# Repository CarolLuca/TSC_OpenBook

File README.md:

# OpenBook

## Introduction

OpenBook is an energy-efficient e-book reader designed with open-source principles, featuring Wi-Fi connectivity and environmental sensing capabilities. The device emphasizes a minimalist design, providing a distraction-free reading experience through a high-contrast e-paper display that mimics real paper, reducing eye strain during extended reading sessions.

## Block Diagram

## Hardware Description

### Microcontroller

The OpenBook is built around the **ESP32-C6-WROOM-1-N8** microcontroller:
- 32-bit RISC-V single-core processor running at up to 160MHz
- 320KB ROM, 512KB HP SRAM, 16KB LP SRAM
- Built-in Wi-Fi 6 and Bluetooth LE 5.0 connectivity
- Support for various interfaces: GPIO, SPI, UART, I2C, PWM
- Operating voltage: 3.3V

The ESP32-C6 offers excellent power efficiency with multiple power modes:
- Active mode: 160-260mA (when running at full capacity)
- Modem sleep: 3-20mA (Wi-Fi radio disabled)
- Light sleep: 0.8mA
- Deep sleep: 10μA (core powered down, wake sources active)
- Hibernation: 2.5μA (minimal functions active)

### Display Interface

The OpenBook connects to a 7.5" E-Paper Display through an FPC connector. The display communicates via SPI:
- EPD_CS connected to ESP32-C6 GPIO10
- EPD_DC connected to ESP32-C6 GPIO5
- EPD_RST connected to ESP32-C6 GPIO23
- EPD_BUSY connected to ESP32-C6 GPIO3
- MOSI, SCK shared with SD card interface

The e-paper display was chosen for its paper-like appearance, ultra-low power consumption (only requires power during page refreshes), and excellent readability in direct sunlight.

### Storage Solutions

The OpenBook features dual storage solutions:

1. **MicroSD Card Interface** (primary storage for e-books):
   - Connected via SPI protocol
   - Card Detect/DAT3 connected to ESP32-C6 GPIO4
   - CMD connected to ESP32-C6 GPIO7 (MOSI for SPI)
   - DAT0 connected to ESP32-C6 GPIO2 (MISO for SPI)
   - CLK connected to ESP32-C6 GPIO6 (SCK for SPI)
   
2. **64MB NOR Flash Memory** (firmware and system storage):
   - Connected via SPI protocol
   - CS connected to ESP32-C6 GPIO11
   - Shares MOSI, MISO, and SCK with the SD card interface
   - Provides reliable non-volatile storage for the operating system and application code

### Real-Time Clock (RTC)

A DS3231SN RTC module maintains accurate timekeeping even when the device is powered off:
- Communicates via I2C protocol
- SCL connected to ESP32-C6 GPIO22
- SDA connected to ESP32-C6 GPIO21
- Reset pin connected to ESP32-C6 GPIO18
- 32KHz output connected to ESP32-C6 GPIO1
- SQW/INT connected to ESP32-C6 GPIO0
- Features a backup battery input for continuous timekeeping
- Temperature-compensated crystal oscillator for high accuracy (+/-2ppm)

### Environmental Sensing

The BME688 environmental sensor provides comprehensive monitoring:
- Digital low-power gas, pressure, temperature, and humidity sensor
- Communicates via I2C (shared bus with RTC)
- SCK connected to ESP32-C6 GPIO22 (SCL for I2C)
- SDI connected to ESP32-C6 GPIO21 (SDA for I2C)
- Control pins connected to ESP32-C6 GPIO19
- Power consumption: 3.7μA at 1Hz sampling rate; 0.15μA in sleep mode
- Temperature range: -40 to +85°C
- Humidity measurement range: 0-100% RH
- Pressure range: 300-1100 hPa

### Power Management

The OpenBook is designed for extended battery life:

1. **USB-C Connector**:
   - Industry-standard charging and data interface
   - Connected to ESP32-C6 via USB lines (GPIO12/GPIO13)
   - ESD protection provided by USBLC6-2SC6Y
   
2. **Li-Po Battery Charging Controller (MCP73831)**:
   - Handles battery charging from USB with programmable charge current
   - Input voltage: 3.75V to 6V
   - Battery output protection circuitry

3. **LDO Voltage Regulator (XC6220A331MR-G)**:
   - Provides stable 3.3V from battery voltage
   - Low quiescent current: 1μA
   - High efficiency operation

4. **Battery Fuel Gauge (MAX17048G+T10)**:
   - Monitors battery charge level using ModelGauge algorithm
   - Communicates via I2C (shared bus with RTC and BME688)
   - SCL connected to ESP32-C6 GPIO22
   - SDA connected to ESP32-C6 GPIO21
   - Power consumption: 23μA active, 3μA hibernate
   - Provides accurate remaining capacity estimation

### User Input

Three physical buttons provide intuitive navigation:
1. **Reset Button**: Connected to ESP32-C6 Enable pin
2. **Boot Button**: Connected to ESP32-C6 GPIO9
3. **Navigation Button**: Connected to ESP32-C6 GPIO15

Each button includes debouncing circuitry to ensure reliable operation.

### Expansion Capability

A Qwiic connector provides expandability:
- Compatible with Stemma QT sensors and modules
- Connects to the I2C bus
- Allows for easy addition of future sensors without soldering

## Pin Allocation of ESP32-C6

| Pin Number | GPIO | Function              | Component                             | Reason for Selection                                    |
|------------|------|------------------------|---------------------------------------|--------------------------------------------------------|
| 3          | EN   | Reset                  | Reset Button                          | Hardware-defined enable pin                             |
| 8          | GPIO0 | SQW/INT               | RTC DS3231SN Interrupt                | Allows RTC-based wakeup from sleep                      |
| 9          | GPIO1 | 32KHz input           | RTC DS3231SN 32KHz output             | Provides precise timing reference                       |
| 27         | GPIO2 | MISO                  | SD Card, E-Paper, NOR Flash           | Hardware SPI MISO line                                  |
| 28         | GPIO3 | EPD_BUSY              | E-Paper Display busy signal           | Status monitoring for display                           |
| 30         | GPIO4 | SD_CS                 | SD Card chip select                   | SPI device selection                                    |
| 31         | GPIO5 | EPD_DC                | E-Paper Display data/command          | Display controller communication                         |
| 32         | GPIO6 | SCK                   | SD Card, E-Paper, NOR Flash           | Hardware SPI clock                                      |
| 33         | GPIO7 | MOSI                  | SD Card, E-Paper, NOR Flash           | Hardware SPI MOSI line                                  |
| 13         | GPIO9 | Boot                  | Boot Button                           | Boot mode selection                                     |
| 14         | GPIO10 | EPD_CS               | E-Paper Display chip select           | SPI device selection                                    |
| 15         | GPIO11 | FLASH_CS             | NOR Flash chip select                 | SPI device selection                                    |
| 16         | GPIO12 | USB_D-               | USB Data negative                     | USB communication                                       |
| 17         | GPIO13 | USB_D+               | USB Data positive                     | USB communication                                       |
| 23         | GPIO15 | Navigation           | Navigation Button                     | User input                                              |
| 16         | GPIO18 | RTC_RST              | RTC reset                             | Reset control for RTC                                   |
| 17         | GPIO19 | I2C_PW               | BME688 power control                  | Power management for sensor                             |
| 19         | GPIO21 | SDA                  | I2C data (RTC, BME688, Battery Gauge) | Hardware I2C data line                                  |
| 20         | GPIO22 | SCL                  | I2C clock (RTC, BME688, Battery Gauge)| Hardware I2C clock line                                 |
| 21         | GPIO23 | EPD_RST              | E-Paper Display reset                 | Display initialization control                          |

## Bill of Materials (BOM)

| Component                     | Description                                   | Price (EUR) | Provider                                                                                                   | Datasheet                                                                                                    |
|-------------------------------|-----------------------------------------------|-------------|------------------------------------------------------------------------------------------------------------|------------------------------------------------------------------------------------------------------------|
| ESP32-C6-WROOM-1-N8          | Main Microcontroller                          | 2.99        | [Mouser](https://eu.mouser.com/ProductDetail/Espressif-Systems/ESP32-C6-WROOM-1U-N8?qs=1Kr7Jg1SGW%2FzPU4G%252ByMwkA%3D%3D) | [Datasheet](https://eu.mouser.com/datasheet/2/891/Espressif_Systems_7_11_2023_esp32_c6_wroom_1_wroom-3236277.pdf) |
| USB4110-GF-A                  | USB-C Connector                               | 0.39        | [Mouser](https://eu.mouser.com/ProductDetail/Same-Sky/UJC-H-G-SMT-2-P6-TR?qs=IKkN%2F947nfApFV8T6rOqww%3D%3D) | [Datasheet](https://eu.mouser.com/datasheet/2/1628/ujc_h_g_smt_2_p6_tr-3511211.pdf)                          |
| USBLC6-2SC6Y                  | USB ESD Protection                            | 0.44        | [Mouser](https://eu.mouser.com/ProductDetail/STMicroelectronics/USBLC6-2SC6Y?qs=gNDSiZmRJS%2FOgDexvXkdow%3D%3D) | [Datasheet](https://eu.mouser.com/datasheet/2/389/usblc6_2sc6y-1852505.pdf)                                   |
| DMG2305UX-7                   | P-Channel MOSFET                              | 0.19 × 2    | [Mouser](https://eu.mouser.com/ProductDetail/Diodes-Incorporated/DMG2305UX-7?qs=L1DZKBg7t5F%2FNBHrjfxC%252Bg%3D%3D) | [Datasheet](https://www.diodes.com/assets/Datasheets/DMG2305UX.pdf)                                           |
| SD0805S020S1R0                | Schottky Diode                                | 0.30 × 2    | [Mouser](https://eu.mouser.com/ProductDetail/KYOCERA-AVX/SD0805S020S1R0?qs=jCA%252BPfw4LHbpkAoSnwrdjw%3D%3D) | [Datasheet](https://eu.mouser.com/datasheet/2/40/schottky-3165252.pdf)                                       |
| XC6220A331MR-G                | LDO Voltage Regulator                         | 1.46        | [Mouser](https://eu.mouser.com/ProductDetail/Torex-Semiconductor/XC6220A331MR-G?qs=AsjdqWjXhJ8ZSWznL1J0gg%3D%3D) | [Datasheet](https://eu.mouser.com/datasheet/2/760/xc6220-3371556.pdf)                                         |
| 293D107X9010D2TE3             | Tantalum Capacitor                            | 0.68        | [Mouser](https://eu.mouser.com/ProductDetail/Vishay-Sprague/293D107X9010D2TE3?qs=8dfOI6wKXonVqFgS8%252BQ%2FMA%3D%3D) | [Datasheet](https://www.vishay.com/docs/40002/293d.pdf)                                                       |
| 112A-TAAR-R03                 | MicroSD Card Socket                           | 1.10        | [Comet](https://store.comet.srl.ro/Catalogue/Product/43497/)                                               | [Datasheet](https://store.comet.bg/download-file.php?id=27596)                                                |
| IFDC5050JZER680M              | 68µH Power Inductor                           | 0.90        | [Mouser](https://eu.mouser.com/ProductDetail/Vishay-Dale/IFDC5050JZER680M?qs=iLKYxzqNS745SePZd8tBoA%3D%3D) | [Datasheet](https://www.vishay.com/docs/34635/ifdc5050jz.pdf)                                                |
| MBR0530-TP                    | Schottky Diode                                | 0.14 × 3    | [Mouser](https://eu.mouser.com/ProductDetail/Micro-Commercial-Components-MCC/MBR0530-TP?qs=KFo7JewZbUECRHkxGanrdg%3D%3D) | [Datasheet](https://eu.mouser.com/datasheet/2/258/MBR0520_MBR0580_SOD123_-2492194.pdf)                      |
| SI1308EDL-T1-GE3              | N-Channel MOSFET                              | 0.42 × 2    | [Mouser](https://eu.mouser.com/ProductDetail/Vishay-Semiconductors/SI1308EDL-T1-GE3?qs=bX1%252BNvsK%2FBramh9tgpOaEw%3D%3D) | [Datasheet](https://www.vishay.com/docs/63399/si1308edl.pdf)                                                |
| KGF21BR71H104KT               | 0.1µF Capacitor                               | 0.30        | [Mouser](https://eu.mouser.com/ProductDetail/KYOCERA-AVX/KGF21BR71H104KT?qs=Jm2GQyTW%2FbjYyKCvVWAEOw%3D%3D) | [Datasheet](https://eu.mouser.com/datasheet/2/40/KGF-3223650.pdf)                                            |
| MAASL105CC7105MFCA01          | 1µF Capacitor                                 | 0.13 × 10   | [Mouser](https://eu.mouser.com/ProductDetail/TAIYO-YUDEN/MAASL105CC7105MFCA01?qs=HFfMDpzxxd1Fn%2FInbJA7vw%3D%3D) | [Datasheet](https://eu.mouser.com/datasheet/2/396/TAIYO_YUDEN_04_27_2024_c_mlcc_A_e1-3451516.pdf)           |
| CM05X5R475M16AH               | 4.7µF Capacitor                               | 0.23 × 5    | [Mouser](https://eu.mouser.com/ProductDetail/KYOCERA-AVX/CM05X5R475M16AH?qs=doiCPypUmgFT1xquZKhWtQ%3D%3D) | [Datasheet](https://eu.mouser.com/datasheet/2/40/Kyocera_AVX_Components_CM025_CM05_CM105_CM21_E217K-2932876.pdf) |
| CGA3EDX7T1A106M080AU          | 10µF Capacitor                                | 0.47        | [Mouser](https://eu.mouser.com/ProductDetail/TDK/CGA3EDX7T1A106M080AU?qs=ZcfC38r4PovL%2FBNBUzzBFw%3D%3D) | [Datasheet](https://product.tdk.com/system/files/dam/doc/product/capacitor/ceramic/mlcc/catalog/mlcc_automotive_general_en.pdf) |
| KAM21BR71H104JT               | 100nF Capacitor                               | 0.30 × 8    | [Mouser](https://eu.mouser.com/ProductDetail/KYOCERA-AVX/KAM21BR71H104JT?qs=Jm2GQyTW%2Fbic6Zk4McEt6w%3D%3D) | [Datasheet](https://eu.mouser.com/datasheet/2/40/AutoMLCCKAM-3216307.pdf)                                    |
| RNCL1210FT50L0                | 0.47Ω Resistor                                | 0.30        | [Mouser](https://eu.mouser.com/ProductDetail/SEI-Stackpole/RNCL1210FT50L0?qs=17ckDYBRdelVLOJ%252BDFjlUw%3D%3D) | [Datasheet](https://eu.mouser.com/datasheet/2/385/sei_rncl-3223524.pdf)                                      |
| RT1206FRE072R2L               | 2.2Ω Resistor                                 | 0.13        | [Mouser](https://eu.mouser.com/ProductDetail/YAGEO/RT1206FRE072R2L?qs=XhSZopxZ3H6S0nYZD83pAA%3D%3D) | [Datasheet](https://eu.mouser.com/datasheet/2/447/PYu_RT_1_to_0_01_RoHS_L_15-3461507.pdf)                    |
| ERA-6AHD150V                  | 15Ω Resistor                                  | 0.25        | [Mouser](https://eu.mouser.com/ProductDetail/Panasonic/ERA-6AHD150V?qs=MNPzkKEzRtQip8ZeekU%252BRw%3D%3D) | [Datasheet](https://industrial.panasonic.com/cdbs/www-data/pdf/RDM0000/AOA0000C307.pdf)                     |
| RP73C2B200RFTDF               | 200Ω Resistor                                 | 0.33        | [Mouser](https://eu.mouser.com/ProductDetail/TE-Connectivity-Holsworthy/RP73C2B200RFTDF?qs=n4i9pByFsMR0dWGpf721CA%3D%3D) | [Datasheet](https://eu.mouser.com/datasheet/2/418/10/ENG_DS_1773272_M1-1588495.pdf)                          |
| ERA-3AED202V                  | 2kΩ Resistor                                  | 0.16        | [Mouser](https://eu.mouser.com/ProductDetail/Panasonic/ERA-3AED202V?qs=yocZuyCaXdM2cBmjcGkIyA%3D%3D) | [Datasheet](https://industrial.panasonic.com/cdbs/www-data/pdf/RDM0000/AOA0000C307.pdf)                     |
| MCS04020C5101FE000            | 5.1kΩ Resistor                                | 0.15 × 2    | [Mouser](https://eu.mouser.com/ProductDetail/Vishay-Beyschlag/MCS04020C5101FE000?qs=wTZ%2FFzl837YsKPLPRIXUbg%3D%3D) | [Datasheet](https://www.vishay.com/docs/28705/mcx0x0xpro.pdf)                                               |
| RNWA0612BTE10K0               | 10kΩ Resistor                                 | 0.32 × 16   | [Mouser](https://eu.mouser.com/ProductDetail/SEI-Stackpole/RNWA0612BTE10K0?qs=IKkN%2F947nfD62pDKWE9ZTQ%3D%3D) | [Datasheet](https://eu.mouser.com/datasheet/2/385/SEI_RNWA-3473840.pdf)                                      |
| ERA-3AED104V                  | 100kΩ Resistor                                | 0.10        | [Mouser](https://eu.mouser.com/ProductDetail/Panasonic/ERA-3AED104V?qs=MNPzkKEzRtQIWcmUWL4kjg%3D%3D) | [Datasheet](https://industrial.panasonic.com/cdbs/www-data/pdf/RDM0000/AOA0000C307.pdf)                     |
| MCP73831-2ACI-MC              | Li-Po Battery Charging Controller             | 0.75        | [Mouser](https://eu.mouser.com/ProductDetail/Microchip-Technology/MCP73831-2ACI-MC?qs=hH%252BOa0VZEiBneYTVdpuVdg%3D%3D) | [Datasheet](https://eu.mouser.com/datasheet/2/268/MCP73831_Family_Data_Sheet_DS20001984H-3441711.pdf)       |
| FH34SRJ-24S-0.5SH(99)         | FPC Connector for E-Paper                     | 2.60        | [Mouser](https://eu.mouser.com/ProductDetail/Hirose-Connector/FH34SRJ-24S-0.5SH99?qs=vcbW%252B4%252BSTIpKBl5ap9J8Fw%3D%3D) | [Datasheet](https://eu.mouser.com/datasheet/2/185/FH34SRJ_24S_0_5SH_99__CL0580_1255_6_99_2DDrawing_0-1615044.pdf) |
| BME688                        | Environmental Sensor                          | 9.86        | [Mouser](https://eu.mouser.com/ProductDetail/Bosch-Sensortec/BME688?qs=IS%252B4QmGtzzqQoVDscqwx3A%3D%3D) | [Datasheet](https://eu.mouser.com/datasheet/2/783/bst_bme688_fl000-2307034.pdf)                              |
| BD5229G-TR                    | Voltage Detector                              | 0.75        | [Mouser](https://eu.mouser.com/ProductDetail/ROHM-Semiconductor/BD5229G-TR?qs=4kLU8WoGk0vvnhrrYwdszw%3D%3D) | [Datasheet](https://fscdn.rohm.com/en/products/databook/datasheet/ic/power/voltage_detector/bd52xxg-e.pdf)  |
| MAX17048G+T10                 | Battery Fuel Gauge                            | 4.28        | [Mouser](https://eu.mouser.com/ProductDetail/Analog-Devices-Maxim-Integrated/MAX17048G%2bT10?qs=D7PJwyCwLAoGnnn8jEPRBQ%3D%3D) | [Datasheet](https://eu.mouser.com/datasheet/2/609/MAX17048_MAX17049-3469099.pdf)                             |
| DS3231SN#                     | RTC Module                                    | 14.91       | [Mouser](https://eu.mouser.com/ProductDetail/Analog-Devices-Maxim-Integrated/DS3231SN?qs=1eQvB6Dk1vhUlr8%2FOrV0Fw%3D%3D) | [Datasheet](https://eu.mouser.com/datasheet/2/609/DS3231-3421123.pdf)                                        |
| CPH3225A                      | RTC Backup Battery                            | 2.33        | [Mouser](https://eu.mouser.com/ProductDetail/Seiko-Semiconductors/CPH3225A?qs=3etwrb1wR%252BhUOph6lAO7eg%3D%3D) | [Datasheet](https://eu.mouser.com/datasheet/2/360/Seiko_Instruments_MicroBattery_E_20230330_2024Jan_-3561061.pdf) |
| PRT-14417                     | Qwiic Connector                               | 3.75        | [Mouser](https://eu.mouser.com/ProductDetail/Adafruit/4208?qs=PzGy0jfpSMtbScLbr0L5dw%3D%3D) | [Datasheet](https://learn.adafruit.com/introducing-adafruit-stemma-qt/technical-specs)                      |
| PGB1010603MR                  | ESD Protection                                | 0.40 × 6    | [Mouser](https://eu.mouser.com/ProductDetail/Littelfuse/PGB1010603MR?qs=gu7KAQ731URLg4GSnNNN7Q%3D%3D) | [Datasheet](https://www.littelfuse.com/assetdocs/pulseguard-esd-suppressors-pgb1-datasheet?assetguid=8a337998-d54d-466b-be4e-dc5bcd1f9321) |
| W25Q512JVEIQ                  | 64MB NOR Flash Memory                         | 5.84        | [Mouser](https://eu.mouser.com/ProductDetail/Winbond/W25Q512JVEIQ?qs=l7cgNqFNU1jw6svr3at6tA%3D%3D) | [Datasheet](https://eu.mouser.com/datasheet/2/949/Winbond_W25Q512JV_Datasheet-3240039.pdf)                   |
| LP584174                      | 2500mAh Li-Po Battery                         | 6.40        | [TME](https://www.tme.eu/en/details/accu-lp584174_cl/rechargeable-batteries/cellevia-batteries/l584174/) | [Datasheet](https://www.tme.eu/Document/e0683d8c34e6d878124489f71bffb6ee/cel0014.pdf)                        |
| MT-DEPG0750BNU590F1           | 7.5" E-Paper Display                          | 48.00       | [Mouser](https://eu.mouser.com/ProductDetail/Microtips-Technology/MT-DEPG0750BNU590F1?qs=DPoM0jnrROVRMMTX0WzK%252Bw%3D%3D) | [Datasheet](https://eu.mouser.com/datasheet/2/271/MT_DEPG0750BNU590F1_V2_7-1894282.pdf)                     |

## Power Consumption Analysis

The OpenBook is designed for maximum battery efficiency:

1. **Peak Power Mode** (Wi-Fi active, display refreshing):
   - ESP32-C6: 160-260mA
   - E-Paper (during refresh): 20-50mA
   - SD Card (active): 30-100mA
   - Other components: ~20-30mA
   - **Total peak consumption**: ~230-440mA

2. **Active Reading Mode** (Wi-Fi disabled, display static):
   - ESP32-C6 (Modem sleep): 3-20mA
   - E-Paper (static): ~0mA
   - SD Card (periodic access): ~5mA average
   - Other components: ~5-10mA
   - **Total active consumption**: ~13-35mA

3. **Standby Mode** (waiting for input):
   - ESP32-C6 (Light sleep): 0.8mA
   - All peripherals in low-power: ~1mA
   - **Total standby consumption**: ~1.8mA

4. **Deep Sleep Mode** (longer periods of inactivity):
   - ESP32-C6 (Deep sleep): 10μA
   - RTC active: 0.2μA
   - Battery monitoring (periodic): ~0.5μA average
   - **Total deep sleep consumption**: ~11μA

With a 2500mAh battery, theoretical runtime estimates:
- Continuous active reading: ~71-192 hours (3-8 days)
- Standby mode: ~1388 hours (~58 days)
- Deep sleep mode: ~227,272 hours (~9,469 days or ~26 years)

In practical usage with mixed operation modes and periodic Wi-Fi synchronization, users can expect 2-4 weeks of regular

Note: props to the Gemini within Google Drawings for helping me with the drawing:)

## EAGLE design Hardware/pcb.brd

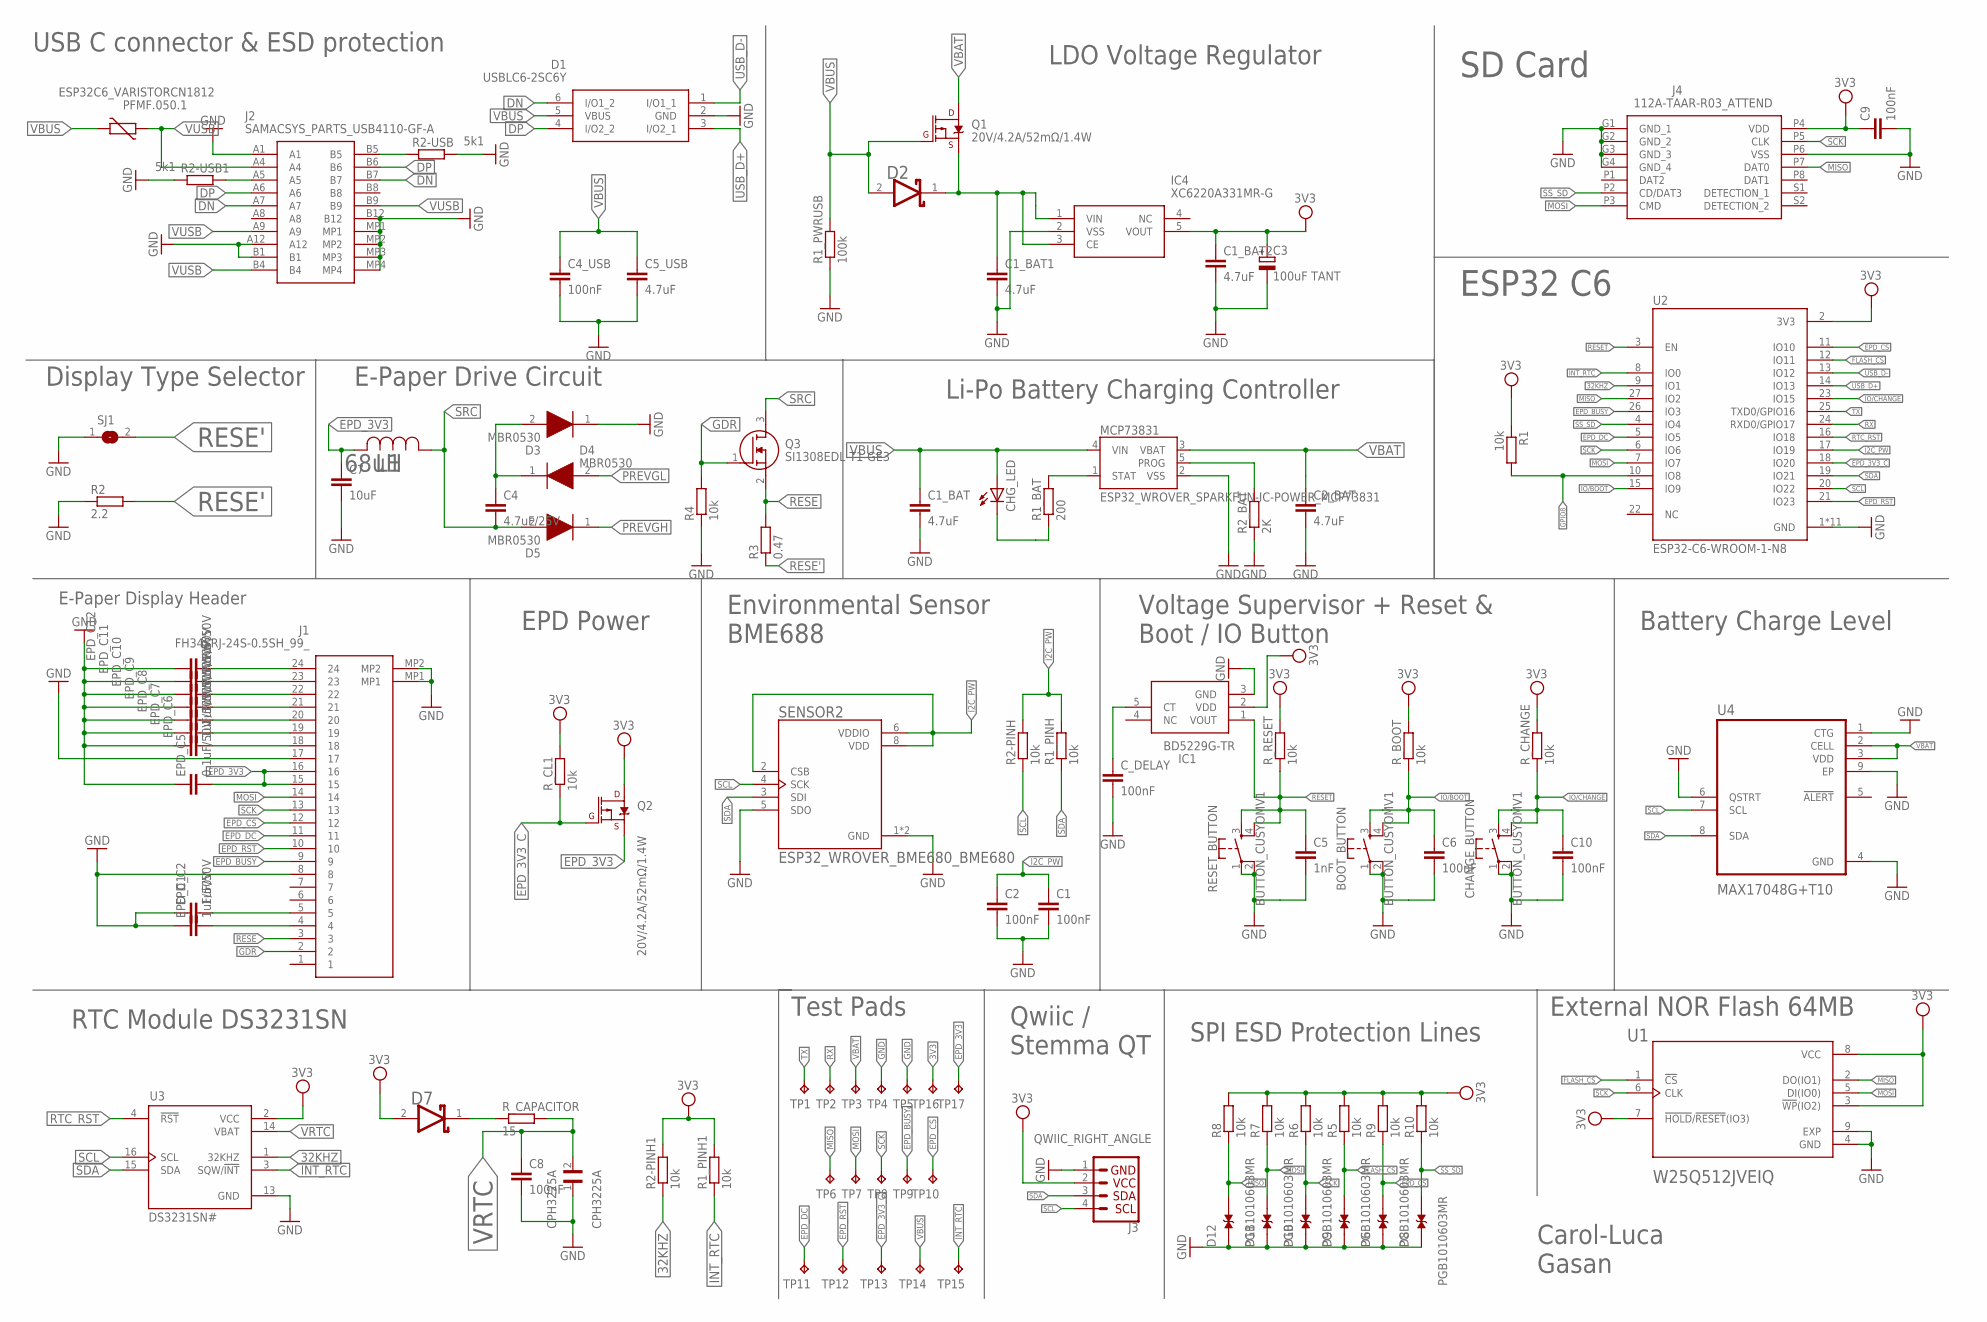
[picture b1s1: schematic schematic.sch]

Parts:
BOOT_BUTTON: BUTTON_CUSYOMV1; MYBUTTON
C1, C2, C4_USB, C6, C8, C9, C10: 100nF; ESP32_WROVER_EAGLE-LTSPICE_C0402
C1_BAT, C1_BAT1, C1_BAT2, C2_BAT, C5_USB: 4.7uF; ESP32_WROVER_EAGLE-LTSPICE_C0402
C3: 100uF TANT; RCL_CT3528
C4: 4.7uF/25V; ESP32_WROVER_EAGLE-LTSPICE_C0402
C5: 1nF; ESP32_WROVER_EAGLE-LTSPICE_C0402
C7: 10uF; ESP32_WROVER_EAGLE-LTSPICE_C0402
CHANGE_BUTTON: BUTTON_CUSYOMV1; MYBUTTON
CHG_LED: ADAFRUIT_LEDCHIP-LED0603; ADAFRUIT_CHIP-LED0603
CPH3225A: CPH3225A; CAPCP3225X100N
C_DELAY: 100nF; ESP32_WROVER_EAGLE-LTSPICE_C0402
D1: USBLC6-2SC6Y; SOT95P280X145-6N
D2, D7: ESP32_WROVER_AVX---SD0805S020S1R0_AVX_SD0805S020S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; ESP32_WROVER_AVX---SD0805S020S1R0_AVX_SD0805S020S1R0_0
D3, D4, D5: MBR0530; SOD3716X135N
D6, D8, D9, D10, D11, D12: PGB1010603MR; DIOC1608X36N
EPD_C1, EPD_C2, EPD_C6, EPD_C7, EPD_C8, EPD_C9, EPD_C10, EPD_C11, EPD_C12: 1uF/50V; ESP32_WROVER_EAGLE-LTSPICE_C0402
EPD_C5: 0.1uF/50V; ESP32_WROVER_EAGLE-LTSPICE_C0402
IC1: BD5229G-TR; SOT95P280X125-5N
IC4: XC6220A331MR-G; SOT95P280X120-5N
J1: FH34SRJ-24S-0.5SH_99_; FH34SRJ24S05SH99
J2: SAMACSYS_PARTS_USB4110-GF-A; SAMACSYS_PARTS_USB4110GFA
J3: QWIIC_RIGHT_ANGLE; JST04_1MM_RA
J4: 112A-TAAR-R03_ATTEND; 112ATAARR03ATTEND
L1: 68uH; IND_4828-WE-TPC_WRE
MCP73831: ESP32_WROVER_SPARKFUN-IC-POWER_MCP73831; ESP32_WROVER_SPARKFUN-IC-POWER_SOT23-5
PFMF.050.1: ESP32C6_VARISTORCN1812; ESP32C6_VARISTOR_CT/CN1812
Q1, Q2: 20V/4.2A/52mΩ/1.4W; ESP32_WROVER_SPARKFUN-DISCRETESEMI_SOT23-3
Q3: SI1308EDL-T1-GE3; SOT65P210X110-3N
R1, R1_PINH, R1_PINH1, R2-PINH, R2-PINH1, R4, R5, R6, R7, R8, R9, R10: 10k; ESP32_WROVER_EAGLE-LTSPICE_R0402
R1_BAT: 200; ESP32_WROVER_EAGLE-LTSPICE_R0402
R1_PWRUSB: 100k; ESP32_WROVER_EAGLE-LTSPICE_R0402
R2: 2.2; ESP32_WROVER_EAGLE-LTSPICE_R0402
R2-USB, R2-USB1: 5k1; ESP32_WROVER_EAGLE-LTSPICE_R0402
R2_BAT: 2K; ESP32_WROVER_EAGLE-LTSPICE_R0402
R3: 0.47; ESP32_WROVER_EAGLE-LTSPICE_R0402
RESET_BUTTON: BUTTON_CUSYOMV1; MYBUTTON
R_BOOT: 10k; ESP32_WROVER_EAGLE-LTSPICE_R0402
R_CAPACITOR: 15; ESP32_WROVER_EAGLE-LTSPICE_R0402
R_CHANGE: 10k; ESP32_WROVER_EAGLE-LTSPICE_R0402
R_CL1: 10k; ESP32_WROVER_EAGLE-LTSPICE_R0402
R_RESET: 10k; ESP32_WROVER_EAGLE-LTSPICE_R0402
SENSOR2: ESP32_WROVER_BME680_BME680; ESP32_WROVER_BME680_PSON80P300X300X100-8N
SJ1: SJ
TP1, TP2, TP3, TP4, TP5, TP6, TP7, TP8, TP9, TP10, TP11, TP12, TP13, TP14, TP15, TP16, TP17: TPTP20R; TP20R
U1: W25Q512JVEIQ; SON127P600X800X80-9N
U2: ESP32-C6-WROOM-1-N8; XCVR_ESP32-C6-WROOM-1-N8
U3: DS3231SN#; SOIC127P1032X265-16N
U4: MAX17048G+T10; SON50P200X200X80-9N

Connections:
3V3: C1_BAT2.1, C3.+, C9.1, D7.2 (ANODE), IC1.2 (VDD), IC4.5 (VOUT), J3.2, J4.P4 (VDD), Q2.3 (D), R1.1, R1_PINH1.2, R2-PINH1.2, R5.2, R6.2, R7.2, R8.2, R9.2, R10.2, R_BOOT.2, R_CHANGE.2, R_CL1.2, R_RESET.2, TP16.TP, U1.3 (!WP!(IO2)), U1.7 (!HOLD!/!RESET!(IO3)), U1.8 (VCC), U2.2 (3V3), U3.2 (VCC)
32KHZ: R2-PINH1.1, U2.9 (IO1), U3.1 (32KHZ)
DN: D1.6 (I/O1_2), J2.A7, J2.B7
DP: D1.4 (I/O2_2), J2.A6, J2.B6
EPD_3V3: C7.1, EPD_C5.2, J1.15, J1.16, L1.2, Q2.2 (S), TP17.TP
EPD_3V3_C: Q2.1 (G), R_CL1.1, TP13.TP, U2.18 (IO20)
EPD_BUSY: J1.9, TP9.TP, U2.26 (IO3)
EPD_CS: D6.2, J1.12, R9.1, TP10.TP, U2.11 (IO10)
EPD_DC: J1.11, TP11.TP, U2.5 (IO5)
EPD_RST: J1.10, TP12.TP, U2.21 (IO23)
FLASH_CS: D9.2, R5.1, U1.1 (!CS), U2.12 (IO11)
GDR: J1.2, Q3.1 (G), R4.2
GND: BOOT_BUTTON.1, BOOT_BUTTON.2, C1.2, C1_BAT.2, C1_BAT1.2, C1_BAT2.2, C2.2, C2_BAT.2, C3.-, C4_USB.2, C5.2, C5_USB.2, C6.2, C7.2, C8.2, C9.2, C10.2, CHANGE_BUTTON.1, CHANGE_BUTTON.2, CPH3225A.1, C_DELAY.2, D1.2 (GND), D3.1 (K), D6.1, D8.1, D9.1, D10.1, D11.1, D12.1, EPD_C1.1, EPD_C2.1, EPD_C5.1, EPD_C6.1, EPD_C7.1, EPD_C8.1, EPD_C9.1, EPD_C10.1, EPD_C11.1, EPD_C12.1, IC1.3 (GND), IC4.2 (VSS), J1.8, J1.17, J1.MP1, J1.MP2, J2.A1, J2.A12, J2.B1, J2.B12, J2.MP1, J2.MP2, J2.MP3, J2.MP4, J3.1, J4.G1 (GND_1), J4.G2 (GND_2), J4.G3 (GND_3), J4.G4 (GND_4), J4.P6 (VSS), MCP73831.2 (VSS), R1_PWRUSB.1, R2.1, R2-USB.2, R2-USB1.1, R2_BAT.1, R4.1, RESET_BUTTON.1, RESET_BUTTON.2, SENSOR2.1 (GND), SENSOR2.5 (SDO), SENSOR2.7 (GND), SJ1.1, TP4.TP, TP5.TP, U1.4 (GND), U1.9 (EXP), U2.1 (GND), U2.28 (GND), U2.29_1 (GND), U2.29_2 (GND), U2.29_3 (GND), U2.29_4 (GND), U2.29_5 (GND), U2.29_6 (GND), U2.29_7 (GND), U2.29_8 (GND), U2.29_9 (GND), U3.13 (GND), U4.1 (CTG), U4.4 (GND), U4.6 (QSTRT), U4.9 (EP)
GPIO8: R1.2, U2.10 (IO8)
I2C_PW: C1.1, C2.1, R1_PINH.2, R2-PINH.2, SENSOR2.2 (CSB), SENSOR2.6 (VDDIO), SENSOR2.8 (VDD), U2.17 (IO19)
INT_RTC: R1_PINH1.1, TP15.TP, U2.8 (IO0), U3.3 (SQW/!INT)
IO/BOOT: BOOT_BUTTON.3, BOOT_BUTTON.4, C6.1, R_BOOT.1, U2.15 (IO9)
IO/CHANGE: C10.1, CHANGE_BUTTON.3, CHANGE_BUTTON.4, R_CHANGE.1, U2.23 (IO15)
MISO: D12.2, J4.P7 (DAT0), R8.1, TP6.TP, U1.2 (DO(IO1)), U2.27 (IO2)
MOSI: D11.2, J1.14, J4.P3 (CMD), R7.1, TP7.TP, U1.5 (DI(IO0)), U2.7 (IO7)
unnamed: J2.B5, R2-USB.1
unnamed: J2.A5, R2-USB1.2
unnamed: C1_BAT1.1, D2.1 (CATHODE), IC4.1 (VIN), IC4.3 (CE), Q1.2 (S)
unnamed: D7.1 (CATHODE), R_CAPACITOR.1
unnamed: MCP73831.5 (PROG), R2_BAT.2
unnamed: MCP73831.1 (STAT), R1_BAT.2
unnamed: CHG_LED.C, R1_BAT.1
unnamed: EPD_C1.2, J1.4
unnamed: EPD_C2.2, J1.5
unnamed: C_DELAY.1, IC1.5 (CT)
unnamed: C4.1, D3.2 (A), D4.1 (K)
unnamed: EPD_C6.2, J1.18
unnamed: EPD_C7.2, J1.19
unnamed: EPD_C8.2, J1.20
unnamed: EPD_C9.2, J1.21
unnamed: EPD_C10.2, J1.22
unnamed: EPD_C11.2, J1.23
unnamed: EPD_C12.2, J1.24
PREVGH: D5.1 (K)
PREVGL: D4.2 (A)
RESE: J1.3, Q3.2 (S), R3.2
RESE': R2.2, R3.1, SJ1.2
RESET: C5.1, IC1.1 (VOUT), RESET_BUTTON.3, RESET_BUTTON.4, R_RESET.1, U2.3 (EN)
RTC_RST: U2.16 (IO18), U3.4 (!RST)
RX: TP2.TP, U2.24 (RXD0/GPIO17)
SCK: D10.2, J1.13, J4.P5 (CLK), R6.1, TP8.TP, U1.6 (CLK), U2.6 (IO6)
SCL: J3.4, R2-PINH.1, SENSOR2.4 (SCK), U2.20 (IO22), U3.16 (SCL), U4.7 (SCL)
SDA: J3.3, R1_PINH.1, SENSOR2.3 (SDI), U2.19 (IO21), U3.15 (SDA), U4.8 (SDA)
SRC: C4.2, D5.2 (A), L1.1, Q3.3 (D)
SS_SD: D8.2, J4.P2 (CD/DAT3), R10.1, U2.4 (IO4)
TX: TP1.TP, U2.25 (TXD0/GPIO16)
USB_D+: D1.3 (I/O2_1), U2.14 (IO13)
USB_D-: D1.1 (I/O1_1), U2.13 (IO12)
VBAT: C2_BAT.1, MCP73831.3 (VBAT), Q1.3 (D), TP3.TP, U4.2 (CELL), U4.3 (VDD)
VBUS: C1_BAT.1, C4_USB.1, C5_USB.1, CHG_LED.A, D1.5 (VBUS), D2.2 (ANODE), MCP73831.4 (VIN), PFMF.050.1.2, Q1.1 (G), R1_PWRUSB.2, TP14.TP
VRTC: C8.1, CPH3225A.2, R_CAPACITOR.2, U3.14 (VBAT)
VUSB: J2.A4, J2.A9, J2.B4, J2.B9, PFMF.050.1.1

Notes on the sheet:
USB C connector & ESD protection
Display Type Selector
SD Card
ESP32 C6
Battery Charge Level
External NOR Flash 64MB
SPI ESD Protection Lines
Qwiic / Stemma QT
Test Pads
RTC Module DS3231SN
LDO Voltage Regulator
EPD Power
Environmental Sensor BME688
Li-Po Battery Charging Controller
E-Paper Drive Circuit
E-Paper Display Header
Voltage Supervisor + Reset & Boot / IO Button
Carol-Luca Gasan

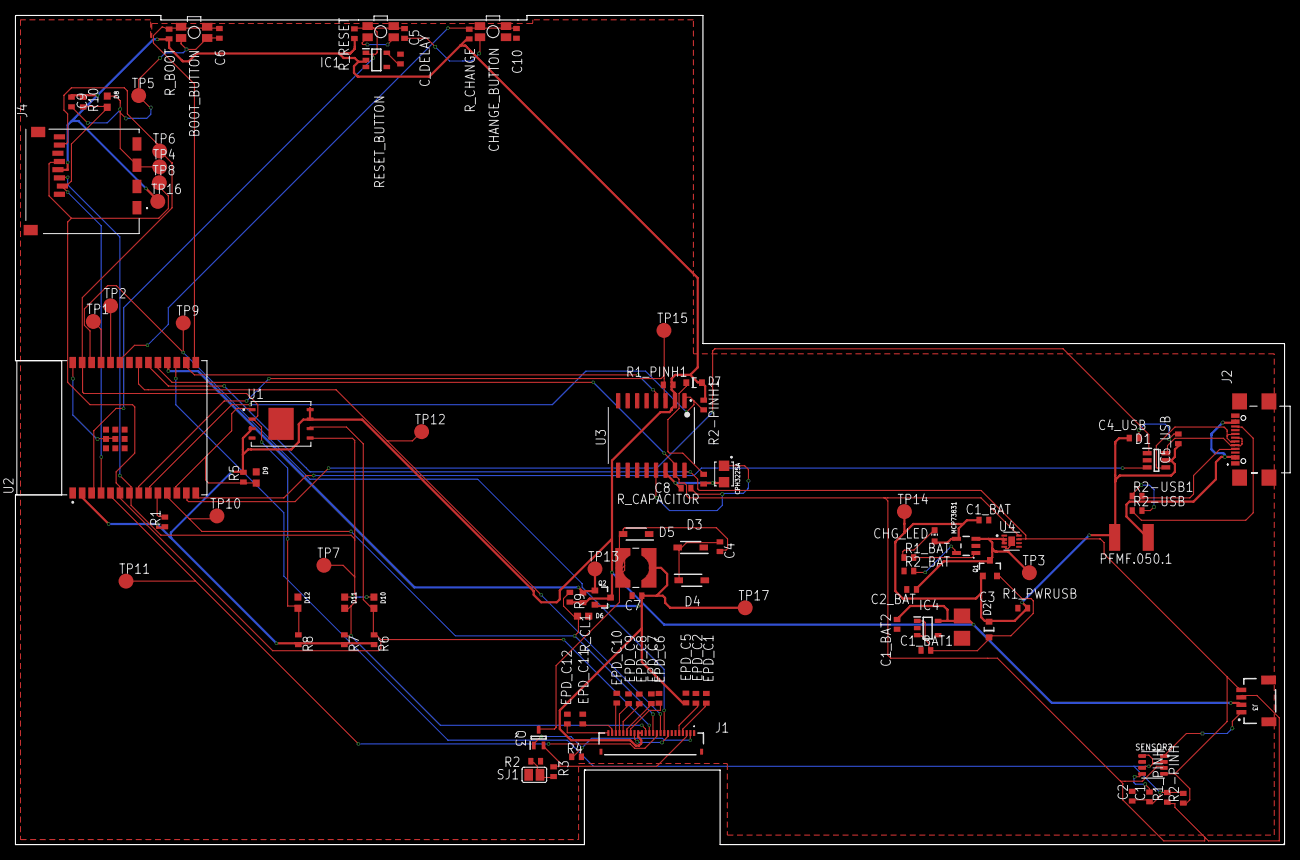
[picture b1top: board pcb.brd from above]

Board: 2 copper layers, 170.2 x 111.2 mm, 103 parts (0 on the bottom side), 55 nets.

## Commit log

2025-04-06 init
2025-04-06 added images
2025-04-06 init readme
2025-04-14 addressed all issues
2025-04-15 quick
2025-04-15 another quick one
2025-04-15 fixed typo

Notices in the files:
parts and their libraries:
COPYRIGHT: Copyright (C) 2024 Ultra Librarian. All rights reserved.
